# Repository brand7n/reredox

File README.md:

# The Redox project repository

NOTE: This a fork Redox called ReRedox. The main difference is even smaller size (removes the outer column of keys).

The Redox project is an open-source, [QMK (Quantum Mechanical Keyboard Firmware)](https://github.com/qmk/qmk_firmware) powered, ergonomic split mechanical keyboard. This repository will be used to share information about the project and instruction on how to use and assembly the Redox keyboard.

**Designer's bio**: [Mattia Dal Ben (aka u/TiaMaT102)](mailto:matthewdibi@gmail.com) obtained a master's degree in Engineering Electronics with a specialization in Computer Science at the University of Udine. Currently works as a Software Engineer in R&D department for a big IoT and Embedded Computers company. Mechanical keyboard enthusiast and maker, the Redox keyboard is the result of all of his passions.

## Rationale

The Redox is a keyboard project designed with ergonomics in mind. It uses Cherry MX style mechanical switches laid out in a 7x5 columnar stagger layout with components that can easily be sourced. 

The design was heavily inspired by the [Ergodox keyboard](https://www.ergodox.io/), and its main goal is to reduce the size without sacrificing too many keys, hence the name **Re**duced Ergo**dox**. 

As an Ergodox user I couldn't ignore the few flaws of the original design and in a moment of arrogance I tried to fix them, thus the Redox features:
- Easier to reach thumb cluster.
- Additional easy-to-reach rotated 1.25u thumb key.
- Reduced size.
- Reduced costs (the Redox uses Arduino Pro Micro instead of the Teensy 2.0).
- Either half can be plugged in to the PC since each half can act as the master.
- Either half can work as a standalone keyboard to be used as a macropad/gaming keyboard.
- RGB backlighting support.
- 3D-printer friendly case.
- Wireless

## Related projects

- [**Redox handwire**](https://www.thingiverse.com/thing:2704567)
  - [Tilted Redox case](https://www.thingiverse.com/thing:2767216): tilted case for the Redox prototype by jschloer.
  - [couscous-kbd](https://github.com/CoenSchalkwijk/couscous-kbd): Redox-inspired parametric OpenSCAD keyboard design.
  - [Redox tenting kit](https://www.thingiverse.com/make:484843): modified base to support tenting, mini-USB for the interconnect, and a hole for microswitch for reset needed when uploading new firmware by [Lenbok](https://github.com/Lenbok).
  - [Iris-inspired Redox case](https://github.com/Lenbok/scad-redox-case): a case inspired both by the Redox rev1.0 and the Iris designed with OpenSCAD by [Lenbok](https://github.com/Lenbok).
  - [Redodactyl keyboard](https://www.reddit.com/r/MechanicalKeyboards/comments/9j5pw5/enter_the_redodactyl_first_build/): handwired 3D printed Dactyl-inspired Redox variant by u/darknao.
- [**Redox rev1.0**](https://github.com/mattdibi/redox-keyboard/tree/master/redox)
	- [3D printed case](https://www.thingiverse.com/thing:2886662), freely available.
	- Rev1.0 PCBs: available at [Falbatech's store](https://falba.tech/product/redox-pcb-electrical-boards-set-of-2/)
	- Commercially available cases:
		- [Falbatech's bamboo cases with tilt kit](https://falba.tech/product/redox-standard-lift-bamboo-wood-case-with-oil-finish/)
		- [Falbatech's fullhand bamboo cases](https://falba.tech/product/redox-fullhand-bamboo-wood-case-with-oil-finish-ver-2/)
		- [Falbatech's PVC cases](https://falba.tech/product/redox-standard-pvc-white-case/)
- [**Redox Wireless (a.k.a. codename Ultron)**](https://github.com/mattdibi/redox-keyboard/tree/master/redox-w)
    - Build logs:
        - [Project log 1](https://hackaday.io/project/160610-redox-keyboard/log/151325-redox-codename-ultron-pt1)
        - [Project log 2](https://hackaday.io/project/160610-redox-keyboard/log/151460-redox-codename-ultron-pt2)
        - [Project log 3](https://hackaday.io/project/160610-redox-keyboard/log/151621-redox-codename-ultron-pt3)
        - [Project log 4](https://hackaday.io/project/160610-redox-keyboard/log/151692-redox-codename-ultron-pt4)
        - [Project log 5](https://hackaday.io/project/160610-redox-keyboard/log/152261-redox-codename-ultron-pt5)
        - [Project log 6](https://hackaday.io/project/160610-redox-keyboard/log/152873-redox-codename-ultron-pt6)
        - [Project log 7](https://hackaday.io/project/160610-redox-keyboard/log/153064-redox-codename-ultron-pt7)
        - [Project log 8](https://hackaday.io/project/160610-redox-keyboard/log/153208-redox-codename-ultron-pt8)
        - [Project log 9](https://hackaday.io/project/160610-redox-keyboard/log/153459-redox-codename-ultron-pt9)
    - [QMK firmware for Redox wireless](https://github.com/mattdibi/qmk_firmware/tree/redox_wireless)
    - [Nordic MCUs firmware for Redox wireless](https://github.com/mattdibi/redox-w-firmware)

### Donations

If you've read this far and found something useful, please consider donating to help me maintain and further develop this project.

<p align="center">

</p>

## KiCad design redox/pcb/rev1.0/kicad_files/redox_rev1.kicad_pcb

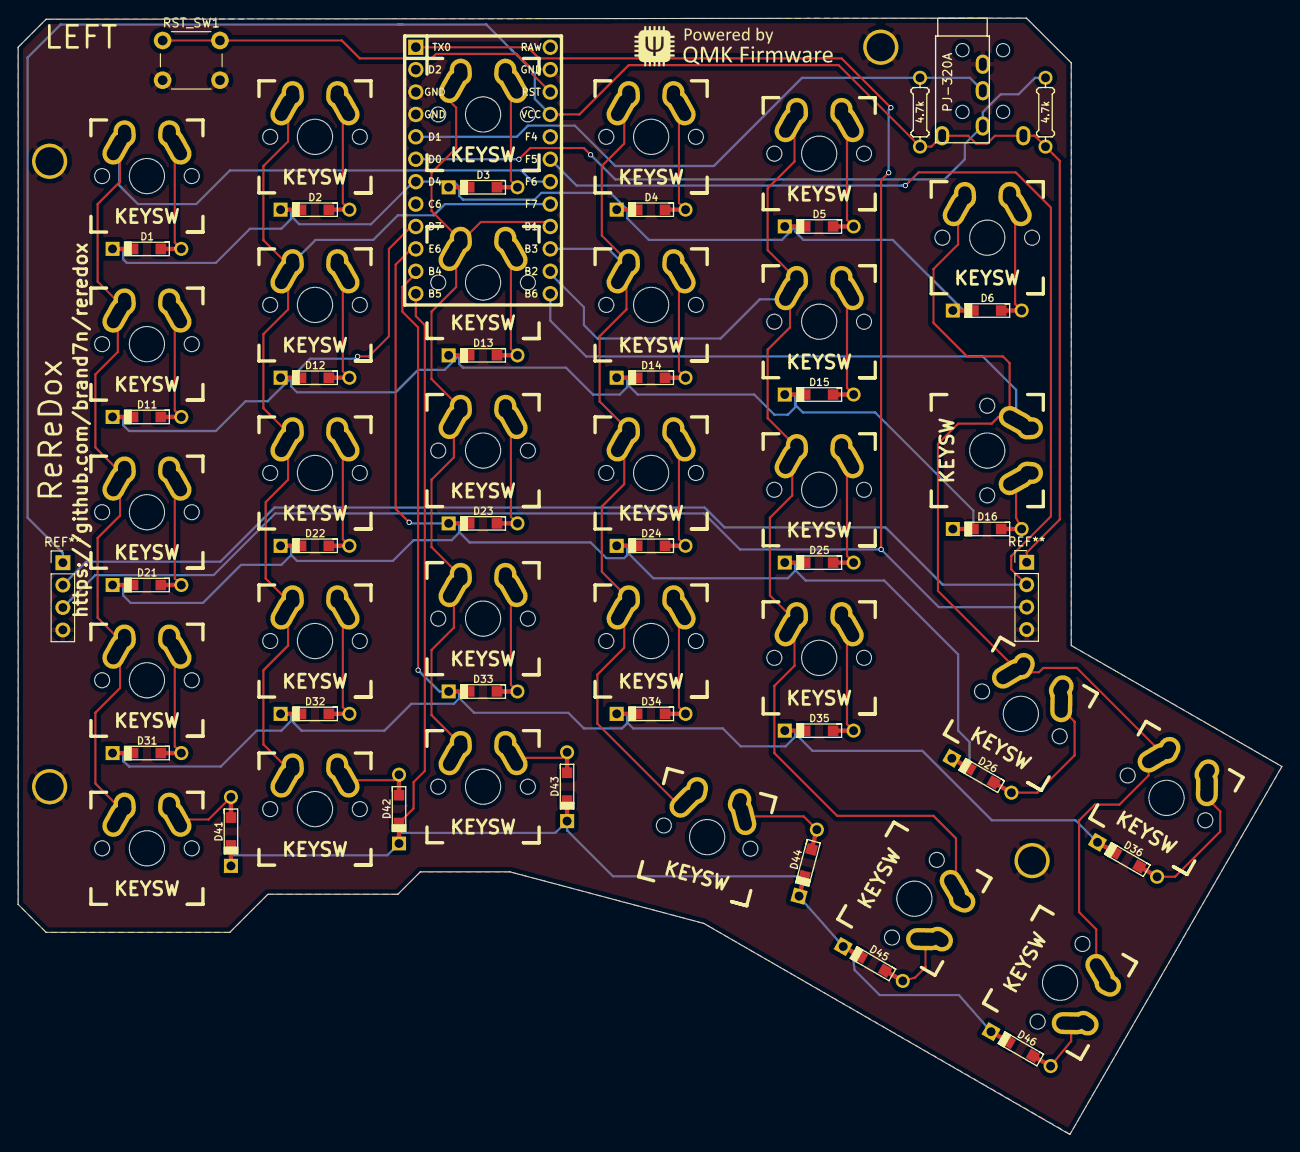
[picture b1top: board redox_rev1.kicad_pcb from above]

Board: 2 copper layers, 143.3 x 126.5 mm, 69 parts (0 on the bottom side), 46 nets.

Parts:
D1, D2, D3, D4, D5, D6, D11, D12, D13, D14, D15, D16, D21, D22, D23, D24, D25, D26, D31, D32, D33, D34, D35, D36, D41, D42, D43, D44, D45, D46: D; Diode-dual
HOLE_M3, HOLE_M3#2, HOLE_M3#3, HOLE_M3#4: VAL**; HOLE_M3
K1, K2, K3, K4, K5, K6, K11, K12, K13, K14, K15, K21, K22, K23, K24, K25, K26, K31, K32, K33, K34, K35, K36, K41, K42, K43: KEYSW; Mx_Alps_100-dualside
K16, K45, K46: KEYSW; Mx_Alps_150-dualsided
K44: KEYSW; Mx_Alps_125-dualside
R1, R2: 4.7k; Resistor-Compact
RST_SW1: SW_PUSH; SW_PUSH_6mm_h4.3mm
TRRS1: Audio-Jack-4; TRRS-PJ-320A-dual
U1: ProMicro; ArduinoProMicro

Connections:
GND: HOLE_M3.1, HOLE_M3#2.1, HOLE_M3#3.1, HOLE_M3#4.1, RST_SW1.2, TRRS1.4, U1.3, U1.4, U1.23
unnamed: D1.2, K1.2
unnamed: D2.2, K2.2
unnamed: D3.2, K3.2
unnamed: D4.2, K4.2
unnamed: D5.2, K5.2
unnamed: D6.2, K6.2
unnamed: D11.2, K11.2
unnamed: D12.2, K12.2
unnamed: D13.2, K13.2
unnamed: D14.2, K14.2
unnamed: D15.2, K15.2
unnamed: D16.2, K16.2
unnamed: D21.2, K21.2
unnamed: D22.2, K22.2
unnamed: D23.2, K23.2
unnamed: D24.2, K24.2
unnamed: D25.2, K25.2
unnamed: D26.2, K26.2
unnamed: D31.2, K31.2
unnamed: D32.2, K32.2
unnamed: D33.2, K33.2
unnamed: D34.2, K34.2
unnamed: D35.2, K35.2
unnamed: D36.2, K36.2
unnamed: D41.2, K41.2
unnamed: D42.2, K42.2
unnamed: D43.2, K43.2
unnamed: D44.2, K44.2
unnamed: D45.2, K45.2
unnamed: D46.2, K46.2
RST: RST_SW1.1, U1.22
SCL: R2.1, TRRS1.2, U1.6
SDA: R1.1, TRRS1.3, U1.5
VCC: R1.2, R2.2, TRRS1.1, U1.21
col1: K1.1, K11.1, K21.1, K31.1, K41.1, U1.18
col2: K2.1, K12.1, K22.1, K32.1, K42.1, U1.17
col3: K3.1, K13.1, K23.1, K33.1, K43.1, U1.16
col4: K4.1, K14.1, K24.1, K34.1, K44.1, U1.15
col5: K5.1, K15.1, K25.1, K35.1, K45.1, U1.14
col6: K6.1, K16.1, K26.1, K36.1, K46.1, U1.13
row0: D1.1, D2.1, D3.1, D4.1, D5.1, D6.1, U1.7
row1: D11.1, D12.1, D13.1, D14.1, D15.1, D16.1, U1.9
row2: D21.1, D22.1, D23.1, D24.1, D25.1, D26.1, U1.10
row3: D31.1, D32.1, D33.1, D34.1, D35.1, D36.1, U1.11
row4: D41.1, D42.1, D43.1, D44.1, D45.1, D46.1, U1.12

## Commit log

2018-10-20 re-redox changes pcb changes
